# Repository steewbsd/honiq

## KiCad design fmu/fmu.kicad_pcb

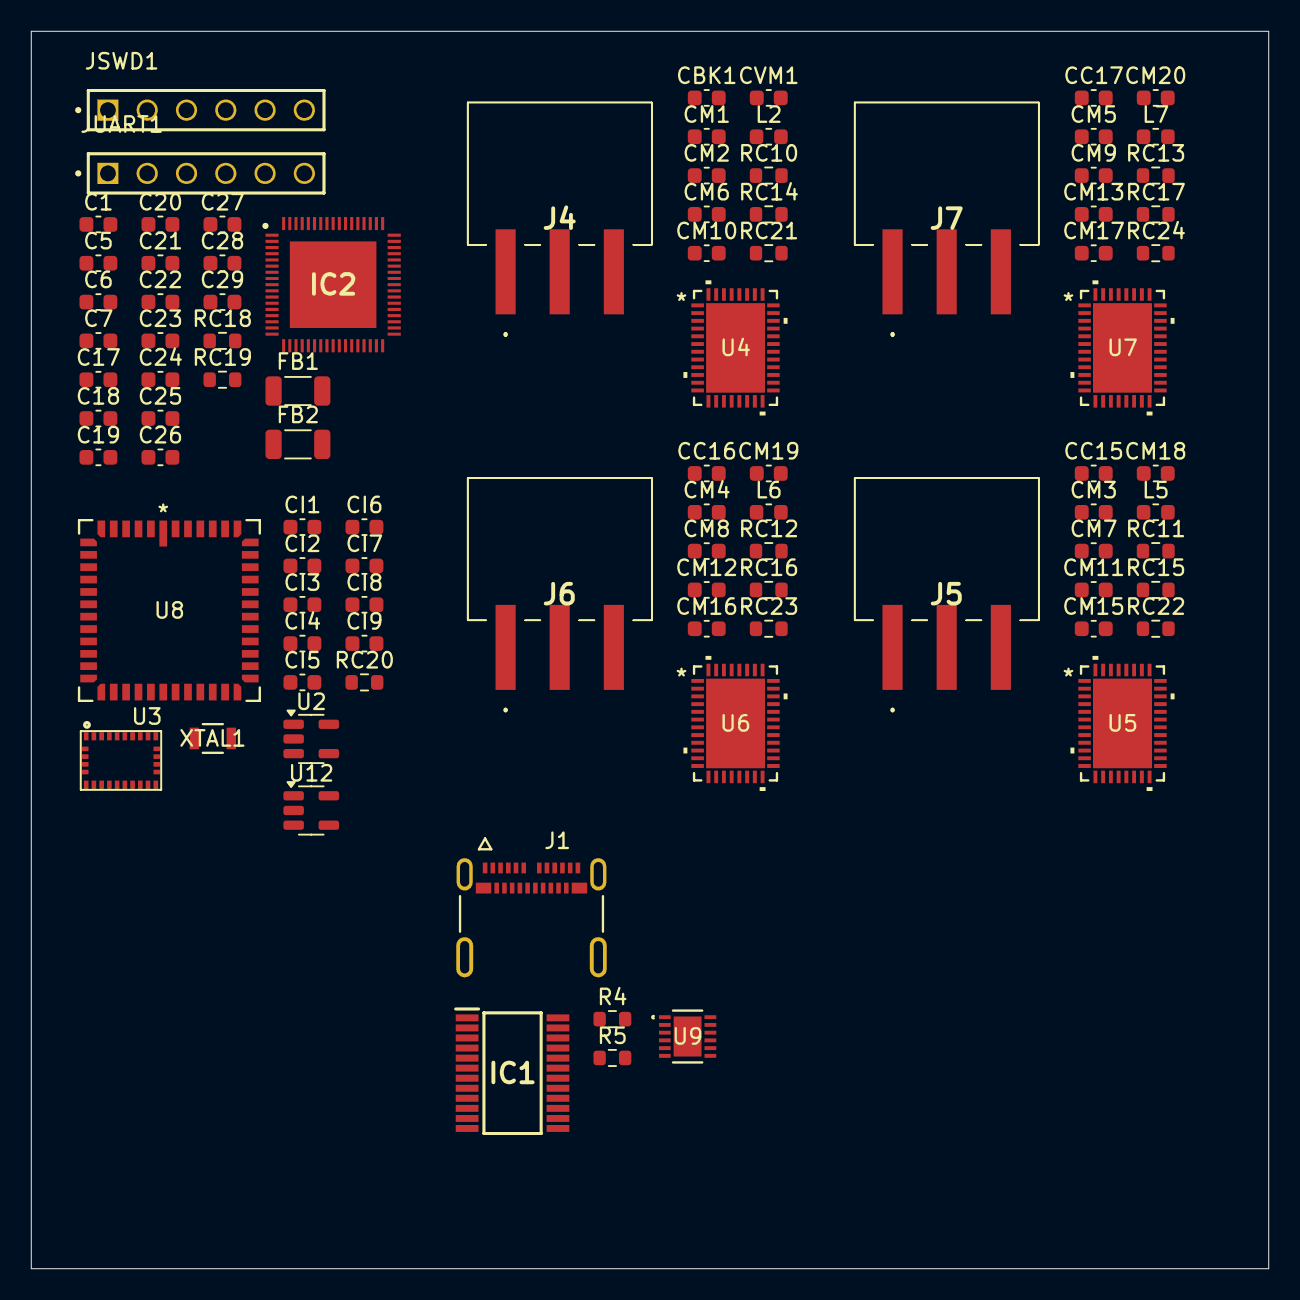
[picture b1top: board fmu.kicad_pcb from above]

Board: 4 copper layers, 80.0 x 80.0 mm, 92 parts (0 on the bottom side), 104 nets, no tracks yet.

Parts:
C1: 10n; C_0603_1608Metric
C5, C18, C19, C21, C24: 0.1u; C_0603_1608Metric
C6, C7, C17, C20, C22, C25: 1u; C_0603_1608Metric
C23: 10u; C_0603_1608Metric
C26, C28, C29: 100p; C_0603_1608Metric
C27: 0.47u; C_0603_1608Metric
CBK1: 1u; C_0603_1608Metric
CC15, CC16, CC17: 47n; C_0603_1608Metric
CI1, CI6, CI7, CI8, CI9: 1u; C_0603_1608Metric
CI2, CI3: 100n; C_0603_1608Metric
CI4, CI5: 22p; C_0603_1608Metric
CM1: 47n; C_0603_1608Metric
CM2, CM3, CM4, CM5, CM6, CM7, CM8, CM9, CM10, CM11, CM12, CM13, CM18, CM19, CM20: 1u; C_0603_1608Metric
CM15, CM16, CM17: 0.1u; C_0603_1608Metric
CVM1: 0.1u; C_0603_1608Metric
FB1: 2512067007Y3; L_1206_3216Metric
FB2: BLM31PG330SN1L; L_1206_3216Metric
IC1: BQ7791500PWT; SOP65P640X120-24N
IC2: EFR32FG28B320F1024IM68-AR; QFN40P800X800X90-69N-D
J1: 1054500101; MOLEX_1054500101
J4, J5, J6, J7: 2213932-3; 22139323
JSWD1: TSW-106-07-G-S; SAMTEC_TSW-106-07-G-S
JUART1: TSW-106-07-G-S; SAMTEC_TSW-106-07-G-S
L2, L5, L6, L7: 2.2u; L_0603_1608Metric
R4, R5: 5.1k; R_0603_1608Metric
RC10, RC11, RC12, RC13, RC14, RC15, RC16, RC17, RC18, RC19: 5.1k; R_0603_1608Metric
RC20, RC21, RC22, RC23, RC24: 10k; R_0603_1608Metric
U2: LP5907MFX-1.8; SOT-23-5
U3: BNO055; LGA28R50P4X10_380X520X100
U4, U5, U6, U7: MCF8316A1VRGFR; VQFN40_RGF_TEX
U8: AR0130CSSC00SPBA0-DR; PLCC48_776AL_OSI
U9: MAX20075ATCA/V+; 21-0664B_MXM
U12: LP5907MFX-2.8; SOT-23-5
XTAL1: ABS07-32.768KHZ-7-T; XTAL_ABS07-32.768KHZ-7-T_ABR

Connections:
+1V8: CI7.2, U2.5 (OUT), U8.3 (VDD), U8.4 (VDD), U8.7 (VDD_IO), U8.8 (VDD_IO), U8.34 (VDD)
+2V8: CI9.2, U8.1 (VDD_PLL), U8.40 (VAA_PIX), U8.41 (VAA_PIX), U8.44 (VAA), U8.45 (VAA), U8.46 (VAA), U12.5 (OUT)
+3.3V: C1.2, C5.2, C7.2, C17.2, C18.2, C19.2, C20.2, C21.2, C22.2, C23.2, C24.2, C27.2, C28.2, CI2.2, CI3.2, CI6.2, CI8.2, FB1.2, FB2.1, IC2.6 (IOVDD_1), IC2.33 (IOVDD_2), IC2.50 (VREGVDD), IC2.52 (DVDD), IC2.53 (AVDD), IC2.54 (IOVDD_3), JSWD1.01, JUART1.01, RC20.1, U2.1 (IN), U3.3 (VDD), U3.28 (VDDIO), U12.1 (IN)
+12V: CM2.1, CM3.1, CM4.1, CM5.1, CM15.2, CM16.2, CM17.2, CVM1.2, U4.9 (VM), U4.10 (VM), U4.11 (VM), U5.9 (VM), U5.10 (VM), U5.11 (VM), U6.9 (VM), U6.10 (VM), U6.11 (VM), U7.9 (VM), U7.10 (VM), U7.11 (VM)
/DIR1: IC2.12 (PC08), U4.34 (DIR)
/DIR2: IC2.13 (PC09), U5.34 (DIR)
/DIR3: IC2.14 (PC10), U6.34 (DIR)
/DIR4: IC2.15 (PC11), U7.34 (DIR)
/FG1: IC2.37 (PA04), RC14.2, U4.29 (FG)
/FG2: IC2.38 (PA05), RC15.2, U5.29 (FG)
/FG3: IC2.39 (PA06), RC16.2, U6.29 (FG)
/FG4: IC2.40 (PA07), RC17.2, U7.29 (FG)
/NFAULT1: IC2.8 (PC04), RC10.2, U4.40 (NFAULT)
/NFAULT2: IC2.9 (PC05), RC11.2, U5.40 (NFAULT)
/NFAULT3: IC2.10 (PC06), RC12.2, U6.40 (NFAULT)
/NFAULT4: IC2.11 (PC07), RC13.2, U7.40 (NFAULT)
/PWM1: IC2.3 (PC00), U4.28 (SPEED/WAKE)
/PWM2: IC2.4 (PC01), U5.28 (SPEED/WAKE)
/PWM3: IC2.5 (PC02), U6.28 (SPEED/WAKE)
/PWM4: IC2.7 (PC03), U7.28 (SPEED/WAKE)
/mcu/AVDD: RC18.1, RC19.1
/mcu/DOUT0: IC2.68 (PD02), U8.28 (DOUT0)
/mcu/DOUT1: IC2.67 (PD03), U8.27 (DOUT1)
/mcu/DOUT2: IC2.66 (PD04), U8.26 (DOUT2)
/mcu/DOUT3: IC2.65 (PD05), U8.25 (DOUT3)
/mcu/DOUT4: IC2.64 (PD06), U8.24 (DOUT4)
/mcu/DOUT5: IC2.63 (PD07), U8.23 (DOUT5)
/mcu/DOUT6: IC2.62 (PD08), U8.22 (DOUT6)
/mcu/DOUT7: IC2.61 (PD09), U8.21 (DOUT7)
/mcu/DOUT8: IC2.60 (PD10), U8.20 (DOUT8)
/mcu/DOUT9: IC2.59 (PD11), U8.19 (DOUT9)
/mcu/DOUT10: IC2.58 (PD12), U8.18 (DOUT10)
/mcu/DOUT11: IC2.57 (PD13), U8.17 (DOUT11)
/mcu/FRAME_VALID: IC2.46 (PA13), U8.15 (FRAME_VALID)
/mcu/IMU_INT: IC2.31 (PB00), U3.14 (INT)
/mcu/IMU_NRST: IC2.32 (PA00), U3.11 (NRESET)
/mcu/LINE_VALID: IC2.47 (PA14), U8.16 (LINE_VALID)
/mcu/NBOOT_LOAD: IC2.30 (PB01), RC20.2, U3.4 (NBOOT_LOAD_PIN)
/mcu/PAVDD: C29.2, FB2.2, IC2.25 (PAVDD)
/mcu/PIXCLK: IC2.45 (PA12), U8.12 (PIXCLK)
/mcu/RESET: IC2.18 (RESETN), JSWD1.05
/mcu/RFVDD: C25.2, C26.2, FB1.1, IC2.19 (RFVDD)
/mcu/SCL: IC2.55 (PD15), RC19.2, U3.19 (COM1), U4.31 (SCL), U5.31 (SCL), U6.31 (SCL), U7.31 (SCL)
/mcu/SDA: IC2.56 (PD14), RC18.2, U3.20 (COM0), U4.30 (SDA), U5.30 (SDA), U6.30 (SDA), U7.30 (SDA)
/mcu/SWDIO: IC2.35 (PA02), JSWD1.03
/mcu/SWO: IC2.36 (PA03), JSWD1.02
/mcu/UART_RXD: IC2.29 (PB02), JUART1.04
/mcu/UART_TXD: IC2.28 (PB03), JUART1.03
/motor1/AVDD: CM10.1, RC10.1, RC14.1, U4.27 (AVDD)
/motor1/BCK_O: CBK1.2, L2.1, U4.3 (FB_BK)
/motor1/OUTA: J4.3, U4.13 (OUTA), U4.14 (OUTA)
/motor1/OUTB: J4.2, U4.16 (OUTB), U4.17 (OUTB)
/motor1/OUTC: J4.1, U4.19 (OUTC), U4.20 (OUTC)
/motor2/AVDD: CM11.1, RC11.1, RC15.1, U5.27 (AVDD)
/motor2/BCK_O: CM18.2, L5.1, U5.3 (FB_BK)
/motor2/OUTA: J5.3, U5.13 (OUTA), U5.14 (OUTA)
/motor2/OUTB: J5.2, U5.16 (OUTB), U5.17 (OUTB)
/motor2/OUTC: J5.1, U5.19 (OUTC), U5.20 (OUTC)
/motor3/AVDD: CM12.1, RC12.1, RC16.1, U6.27 (AVDD)
/motor3/BCK_O: CM19.2, L6.1, U6.3 (FB_BK)
/motor3/OUTA: J6.3, U6.13 (OUTA), U6.14 (OUTA)
/motor3/OUTB: J6.2, U6.16 (OUTB), U6.17 (OUTB)
/motor3/OUTC: J6.1, U6.19 (OUTC), U6.20 (OUTC)
/motor4/AVDD: CM13.1, RC13.1, RC17.1, U7.27 (AVDD)
/motor4/BCK_O: CM20.2, L7.1, U7.3 (FB_BK)
/motor4/OUTA: J7.3, U7.13 (OUTA), U7.14 (OUTA)
/motor4/OUTB: J7.2, U7.16 (OUTB), U7.17 (OUTB)
/motor4/OUTC: J7.1, U7.19 (OUTC), U7.20 (OUTC)
/power/D+: J1.A6 (D1+), J1.B6 (D2+)
/power/D-: J1.A7 (D1-), J1.B7 (D2-)
/power/VBUS: J1.A4 (VBUS_A4), J1.A9 (VBUS_A9), J1.B4 (VBUS_B4), J1.B9 (VBUS_B9)
/sensor/XIN32: CI5.1, U3.27 (XIN32), XTAL1.2
/sensor/XOUT32: CI4.1, U3.26 (XOUT32), XTAL1.1
GND: C1.1, C5.1, C6.1, C7.1, C17.1, C18.1, C19.1, C20.1, C21.1, C22.1, C23.1, C24.1, C25.1, C26.1, C27.1, C28.1, C29.1, CBK1.1, CI1.1, CI2.1, CI3.1, CI4.2, CI5.2, CI6.1, CI7.1, CI8.1, CI9.1, CM6.1, CM7.1, CM8.1, CM9.1, CM10.2, CM11.2, CM12.2, CM13.2, CM18.1, CM19.1, CM20.1, IC1.9 (VSS), IC1.10 (SRP), IC1.16 (CBI), IC1.23 (CTRC), IC1.24 (CTRD), IC2.20 (RFVSS), IC2.51 (VREGVSS), IC2.69 (VSS), J1.A1 (GND_A1), J1.A12 (GND_A12), J1.B1 (GND_B1), J1.B12 (GND_B12), J1.SH1 (SHIELD3), J1.SH2 (SHIELD4), J1.SH3 (SHIELD1), J1.SH4 (SHIELD2), JSWD1.06, JUART1.06, R4.2, R5.1, U2.2 (GND), U3.2 (GND), U3.5 (PS1), U3.6 (PS0), U3.17 (COM3), U3.18 (COM2), U3.25 (GNDIO), U4.2 (DGND), U4.4 (GND_BK), U4.21 (DRVOFF), U4.26 (AGND), U4.41 (GND), U5.2 (DGND), U5.4 (GND_BK), U5.21 (DRVOFF), U5.26 (AGND), U5.41 (GND), U6.2 (DGND), U6.4 (GND_BK), U6.21 (DRVOFF), U6.26 (AGND), U6.41 (GND), U7.2 (DGND), U7.4 (GND_BK), U7.21 (DRVOFF), U7.26 (AGND), U7.41 (GND), U8.2 (DGND), U8.5 (DGND), U8.6 (DGND), U8.38 (AGND), U8.39 (AGND), U8.42 (AGND), U8.43 (AGND), U8.47 (AGND), U8.48 (AGND), U12.2 (GND)
GNDPWR: CM15.1, CM16.1, CM17.1, CVM1.1, RC21.2, RC22.2, RC23.2, RC24.2, U4.12 (PGND), U4.15 (PGND), U4.18 (PGND), U5.12 (PGND), U5.15 (PGND), U5.18 (PGND), U6.12 (PGND), U6.15 (PGND), U6.18 (PGND), U7.12 (PGND), U7.15 (PGND), U7.18 (PGND)
unnamed: IC1.3 (VC5), IC1.4 (VC4), IC1.5 (VC3)
unnamed: C6.2, IC2.48 (DECOUPLE)
unnamed: J1.A5 (CC1), R5.2
unnamed: J1.B5 (CC2), R4.1
unnamed: CI1.2, U3.9 (CAP)
unnamed: RC21.1, U4.35 (BRAKE)
unnamed: CM2.2, U4.8 (CP)
unnamed: CM1.1, U4.7 (CPH)
unnamed: CM1.2, U4.6 (CPL)
unnamed: CM6.2, U4.1 (DVDD)
unnamed: L2.2, U4.5 (SW_BK)
unnamed: RC22.1, U5.35 (BRAKE)
unnamed: CM3.2, U5.8 (CP)
unnamed: CC15.1, U5.7 (CPH)
unnamed: CC15.2, U5.6 (CPL)
unnamed: CM7.2, U5.1 (DVDD)
unnamed: L5.2, U5.5 (SW_BK)
unnamed: RC23.1, U6.35 (BRAKE)
unnamed: CM4.2, U6.8 (CP)
unnamed: CC16.1, U6.7 (CPH)
unnamed: CC16.2, U6.6 (CPL)
unnamed: CM8.2, U6.1 (DVDD)
unnamed: L6.2, U6.5 (SW_BK)
unnamed: RC24.1, U7.35 (BRAKE)
unnamed: CM5.2, U7.8 (CP)
unnamed: CC17.1, U7.7 (CPH)
unnamed: CC17.2, U7.6 (CPL)
unnamed: CM9.2, U7.1 (DVDD)
unnamed: L7.2, U7.5 (SW_BK)

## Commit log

2024-04-15 Start version control of Kicad project
2024-04-15 Replace nRF52840 with EFR32FG28
2024-04-15 Add new logo
2024-04-16 Connect motors and MCU
2024-04-16 Add voltage regulators
2024-04-16 Fix some connections
2024-04-16 Implement battery charger
2024-04-22 Start wiring battery protector; mark charger as non-BOM
2024-04-22 BQ7791500 almost completed
2024-04-23 Add SD Card reader
